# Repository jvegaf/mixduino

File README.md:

# Mixduino
An evolution of Open Source DJ MIDI Controllers
## Main Features
- 3 Complete Channels Mixer 
- 2 Decks  
- Library Browser with song preview function
- 16 Control Pads with RGB Leds (8/Deck)
- FX Controls
- 75 mm pitch/tempo controls
- Multitouch bars instead Jog Wheels
- Compact size enought to take in a backpack (360x260mm) 
## Note
This project actually are WIP.
## Previews

</br>

</br>

</br>

</br>

.
.
.

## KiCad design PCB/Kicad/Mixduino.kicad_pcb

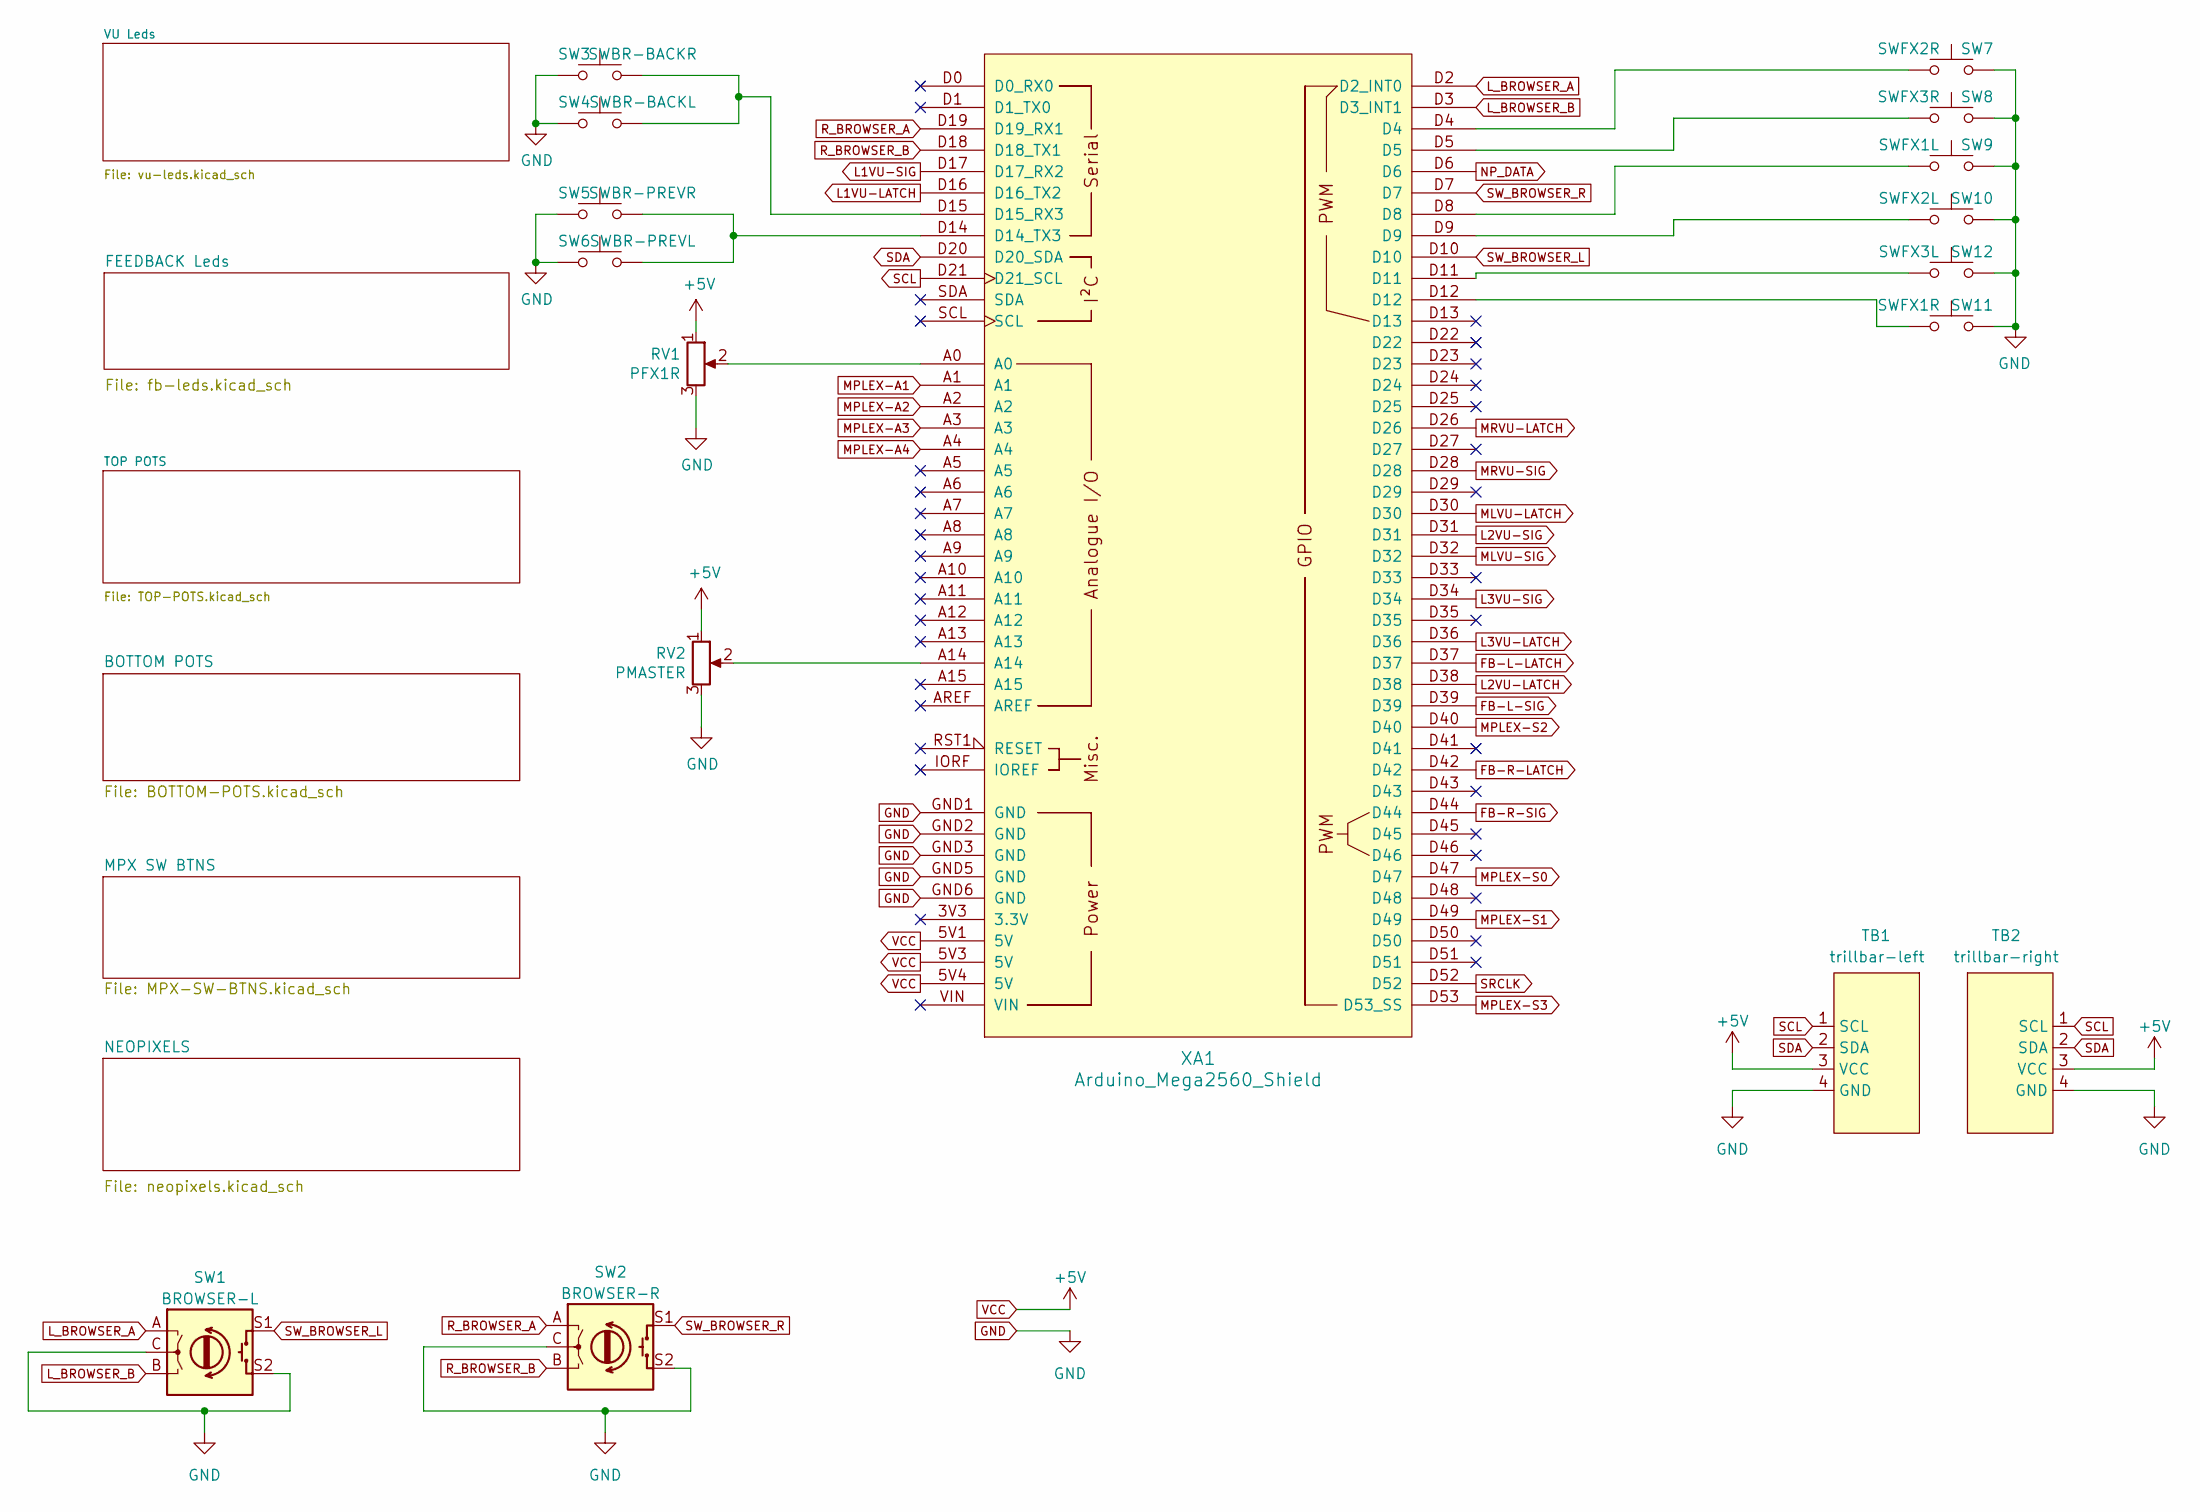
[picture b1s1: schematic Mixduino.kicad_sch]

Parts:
RV1: PFX1R; Potentiometer_Bourns_PTV09A-1_Single_Vertical
RV2: PMASTER; Potentiometer_Bourns_PTV09A-1_Single_Vertical
SW1: BROWSER-L; RotaryEncoder_Alps_EC11E-Switch_Vertical_H20mm_CircularMoun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
SW2: BROWSER-R; RotaryEncoder_Alps_EC11E-Switch_Vertical_H20mm_CircularMoun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
SW3: SWBR-BACKR; SW_Push_1P1T_NO_6x6mm_H8mm
SW4: SWBR-BACKL; SW_Push_1P1T_NO_6x6mm_H8mm
SW5: SWBR-PREVR; SW_Push_1P1T_NO_6x6mm_H8mm
SW6: SWBR-PREVL; SW_Push_1P1T_NO_6x6mm_H8mm
SW7: SWFX2R; SW_Push_1P1T_NO_6x6mm_H8mm
SW8: SWFX3R; SW_Push_1P1T_NO_6x6mm_H8mm
SW9: SWFX1L; SW_Push_1P1T_NO_6x6mm_H8mm
SW10: SWFX2L; SW_Push_1P1T_NO_6x6mm_H8mm
SW11: SWFX1R; SW_Push_1P1T_NO_6x6mm_H8mm
SW12: SWFX3L; SW_Push_1P1T_NO_6x6mm_H8mm
TB1: trillbar-left; JST_XHP_XH-A-1_1x04_P2.54mm_Horizontal
TB2: trillbar-right; JST_XHP_XH-A-1_1x04_P2.54mm_Horizontal
XA1: Arduino_Mega2560_Shield

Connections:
FB-L-LATCH: XA1.D37; also elsewhere on the board
FB-L-SIG: XA1.D39; also elsewhere on the board
FB-R-LATCH: XA1.D42; also elsewhere on the board
FB-R-SIG: XA1.D44; also elsewhere on the board
GND: RV1.3, RV2.3, SW1.C, SW1.S2, SW2.C, SW2.S2, SW3.1, SW4.1, SW5.1, SW6.1, SW7.1, SW8.1, SW9.1, SW10.1, SW11.1, SW12.1, TB1.4 (GND), TB2.4 (GND), XA1.GND1 (GND), XA1.GND2 (GND), XA1.GND3 (GND), XA1.GND5 (GND), XA1.GND6 (GND); also elsewhere on the board
L1VU-LATCH: XA1.D16 (D16_TX2); also elsewhere on the board
L1VU-SIG: XA1.D17 (D17_RX2); also elsewhere on the board
L2VU-LATCH: XA1.D38; also elsewhere on the board
L2VU-SIG: XA1.D31; also elsewhere on the board
L3VU-LATCH: XA1.D36; also elsewhere on the board
L3VU-SIG: XA1.D34; also elsewhere on the board
L_BROWSER_A: SW1.A, XA1.D2 (D2_INT0)
L_BROWSER_B: SW1.B, XA1.D3 (D3_INT1)
MLVU-LATCH: XA1.D30; also elsewhere on the board
MLVU-SIG: XA1.D32; also elsewhere on the board
MPLEX-A1: XA1.A1; also elsewhere on the board
MPLEX-A2: XA1.A2; also elsewhere on the board
MPLEX-A3: XA1.A3; also elsewhere on the board
MPLEX-A4: XA1.A4; also elsewhere on the board
MPLEX-S0: XA1.D47; also elsewhere on the board
MPLEX-S1: XA1.D49; also elsewhere on the board
MPLEX-S2: XA1.D40; also elsewhere on the board
MPLEX-S3: XA1.D53 (D53_SS); also elsewhere on the board
MRVU-LATCH: XA1.D26; also elsewhere on the board
MRVU-SIG: XA1.D28; also elsewhere on the board
NP_DATA: XA1.D6; also elsewhere on the board
unnamed: RV1.2, XA1.A0
unnamed: RV2.2, XA1.A14
unnamed: SW3.2, SW4.2, XA1.D15 (D15_RX3)
unnamed: SW5.2, SW6.2, XA1.D14 (D14_TX3)
unnamed: SW7.2, XA1.D4
unnamed: SW8.2, XA1.D5
unnamed: SW9.2, XA1.D8
unnamed: SW10.2, XA1.D9
unnamed: SW11.2, XA1.D12
unnamed: SW12.2, XA1.D11
R_BROWSER_A: SW2.A, XA1.D19 (D19_RX1)
R_BROWSER_B: SW2.B, XA1.D18 (D18_TX1)
SCL: TB1.1 (SCL), TB2.1 (SCL), XA1.D21 (D21_SCL)
SDA: TB1.2 (SDA), TB2.2 (SDA), XA1.D20 (D20_SDA)
SRCLK: XA1.D52; also elsewhere on the board
SW_BROWSER_L: SW1.S1, XA1.D10
SW_BROWSER_R: SW2.S1, XA1.D7
VCC: RV1.1, RV2.1, TB1.3 (VCC), TB2.3 (VCC), XA1.5V1 (5V), XA1.5V3 (5V), XA1.5V4 (5V); also elsewhere on the board

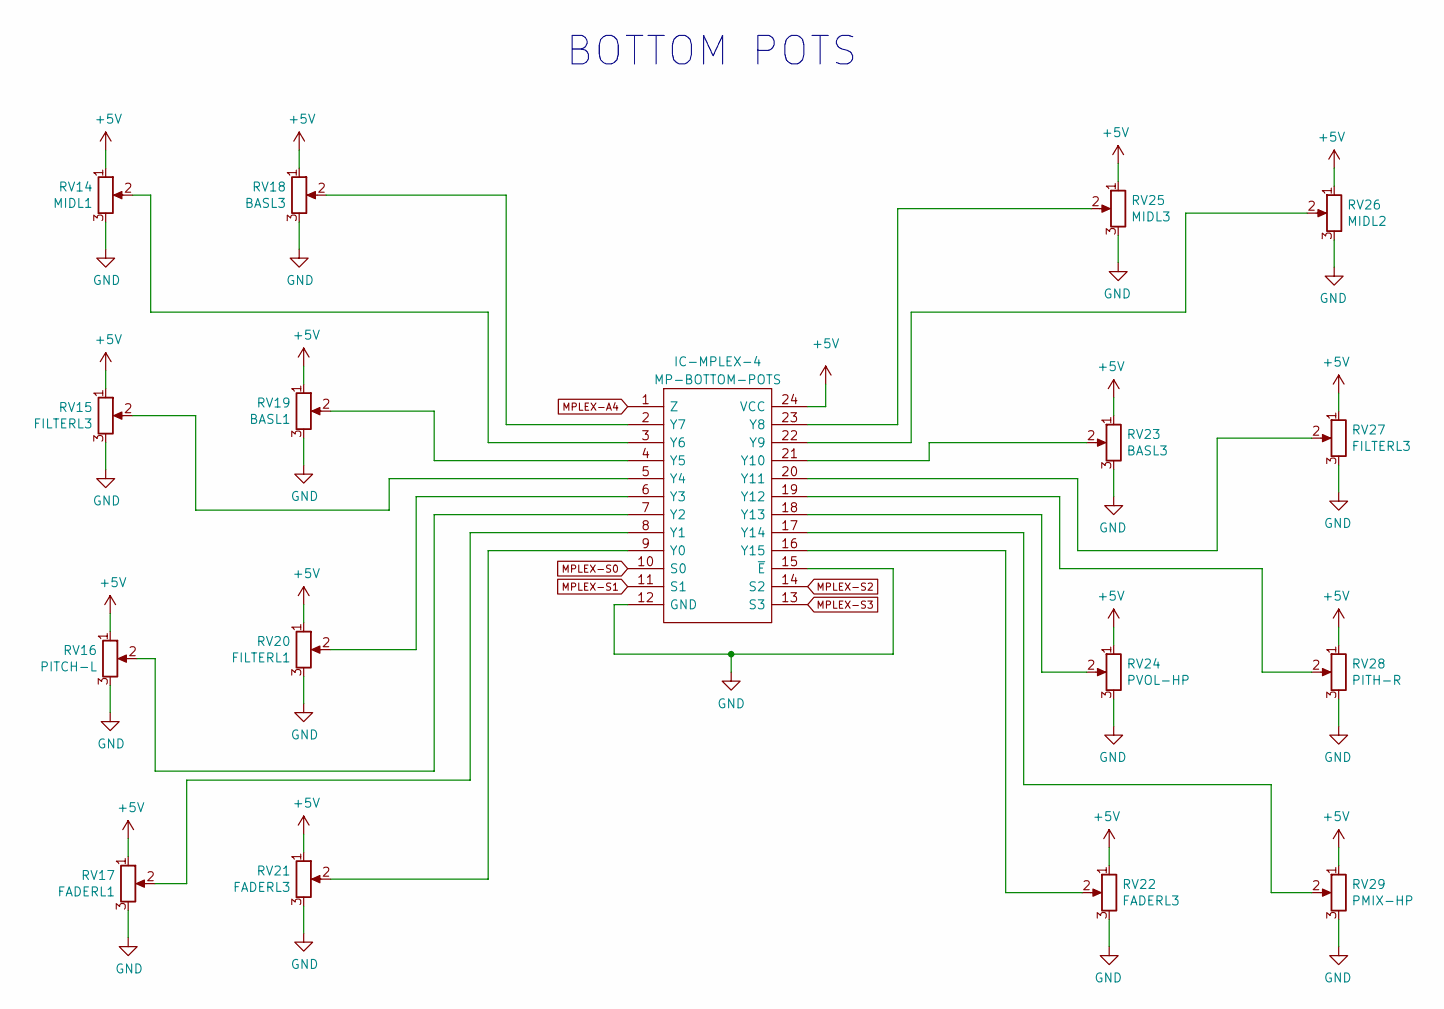
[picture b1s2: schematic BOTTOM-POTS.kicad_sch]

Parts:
IC-MPLEX-4: MP-BOTTOM-POTS; SOIC-24W_7.5x15.4mm_P1.27mm; Mouser Part Number 771-HC4067D653
RV14: MIDL1; Potentiometer_Bourns_PTV09A-1_Single_Vertical
RV15, RV27: FILTERL3; Potentiometer_Bourns_PTV09A-1_Single_Vertical
RV16: PITCH-L; fader-L75
RV17: FADERL1; fader-L60
RV18, RV23: BASL3; Potentiometer_Bourns_PTV09A-1_Single_Vertical
RV19: BASL1; Potentiometer_Bourns_PTV09A-1_Single_Vertical
RV20: FILTERL1; Potentiometer_Bourns_PTV09A-1_Single_Vertical
RV21, RV22: FADERL3; fader-L60
RV24: PVOL-HP; Potentiometer_Bourns_PTV09A-1_Single_Vertical
RV25: MIDL3; Potentiometer_Bourns_PTV09A-1_Single_Vertical
RV26: MIDL2; Potentiometer_Bourns_PTV09A-1_Single_Vertical
RV28: PITH-R; fader-L75
RV29: PMIX-HP; Potentiometer_Bourns_PTV09A-1_Single_Vertical

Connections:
GND: IC-MPLEX-4.12 (GND), IC-MPLEX-4.15 (~E), RV14.3, RV15.3, RV16.3, RV17.3, RV18.3, RV19.3, RV20.3, RV21.3, RV22.3, RV23.3, RV24.3, RV25.3, RV26.3, RV27.3, RV28.3, RV29.3; also elsewhere on the board
MPLEX-A4: IC-MPLEX-4.1 (Z); also elsewhere on the board
MPLEX-S0: IC-MPLEX-4.10 (S0); also elsewhere on the board
MPLEX-S1: IC-MPLEX-4.11 (S1); also elsewhere on the board
MPLEX-S2: IC-MPLEX-4.14 (S2); also elsewhere on the board
MPLEX-S3: IC-MPLEX-4.13 (S3); also elsewhere on the board
unnamed: IC-MPLEX-4.2 (Y7), RV18.2
unnamed: IC-MPLEX-4.3 (Y6), RV14.2
unnamed: IC-MPLEX-4.4 (Y5), RV19.2
unnamed: IC-MPLEX-4.5 (Y4), RV15.2
unnamed: IC-MPLEX-4.6 (Y3), RV20.2
unnamed: IC-MPLEX-4.7 (Y2), RV16.2
unnamed: IC-MPLEX-4.8 (Y1), RV17.2
unnamed: IC-MPLEX-4.9 (Y0), RV21.2
unnamed: IC-MPLEX-4.16 (Y15), RV22.2
unnamed: IC-MPLEX-4.17 (Y14), RV29.2
unnamed: IC-MPLEX-4.18 (Y13), RV24.2
unnamed: IC-MPLEX-4.19 (Y12), RV28.2
unnamed: IC-MPLEX-4.20 (Y11), RV27.2
unnamed: IC-MPLEX-4.21 (Y10), RV23.2
unnamed: IC-MPLEX-4.22 (Y9), RV26.2
unnamed: IC-MPLEX-4.23 (Y8), RV25.2
VCC: IC-MPLEX-4.24 (VCC), RV14.1, RV15.1, RV16.1, RV17.1, RV18.1, RV19.1, RV20.1, RV21.1, RV22.1, RV23.1, RV24.1, RV25.1, RV26.1, RV27.1, RV28.1, RV29.1; also elsewhere on the board

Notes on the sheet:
BOTTOM POTS

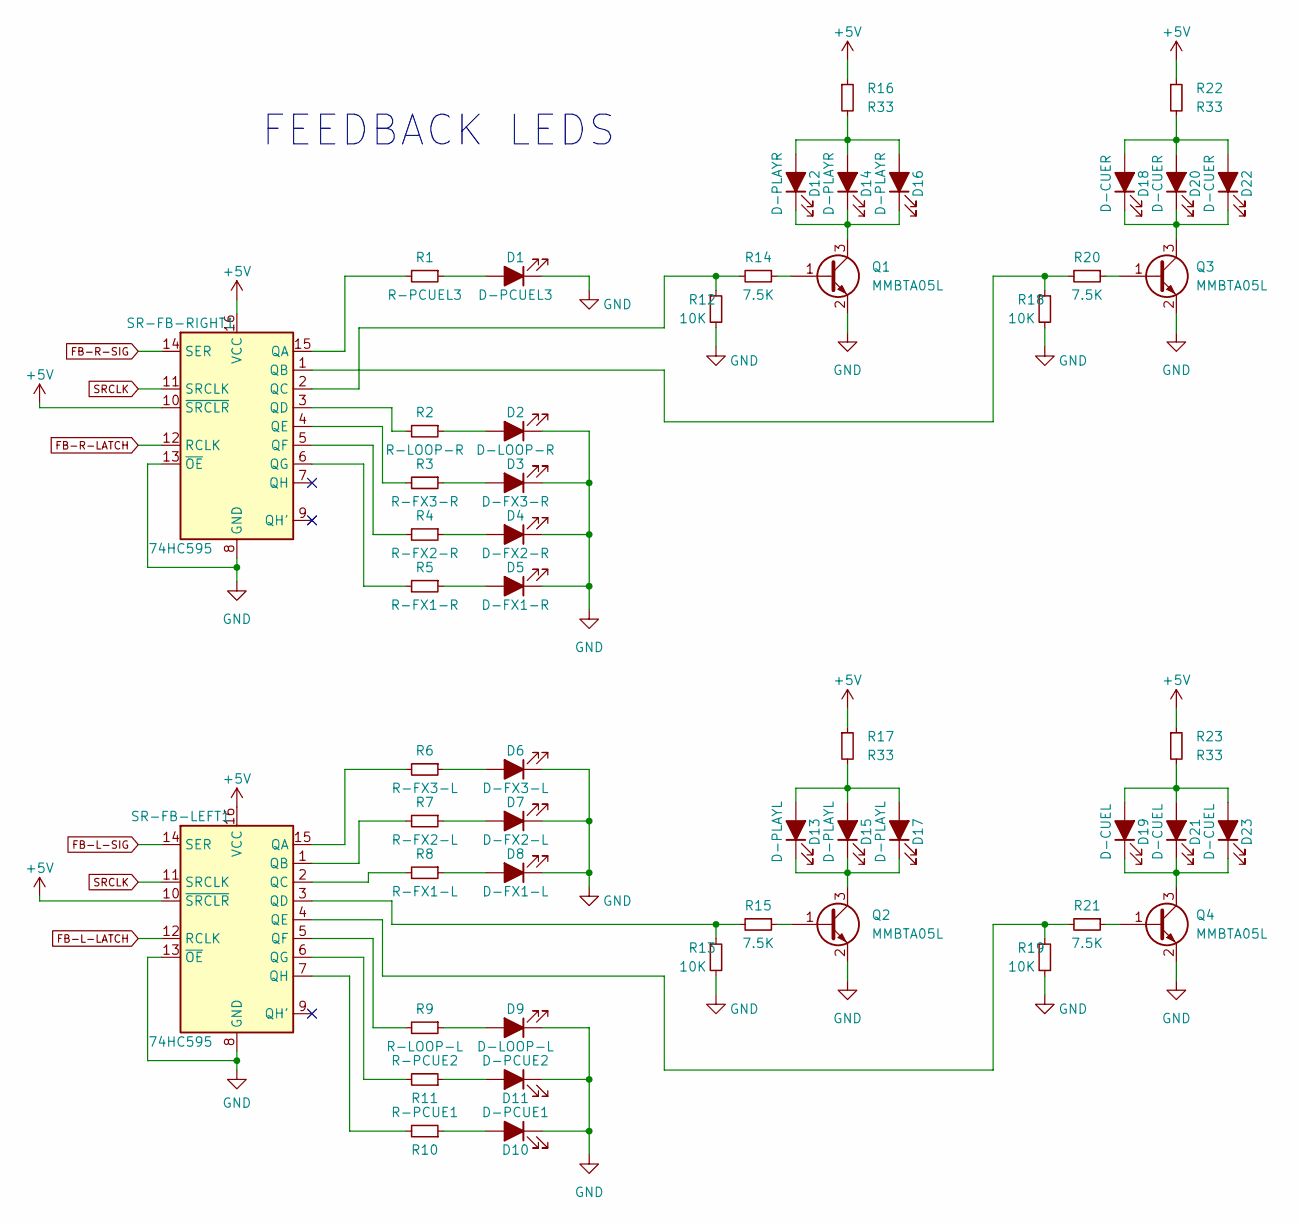
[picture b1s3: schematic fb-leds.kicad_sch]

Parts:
D1: D-PCUEL3; LED_1206_3216Metric_Pad1.42x1.75mm_HandSolder
D2: D-LOOP-R; LED_1206_3216Metric_Pad1.42x1.75mm_HandSolder
D3: D-FX3-R; LED_1206_3216Metric_Pad1.42x1.75mm_HandSolder
D4: D-FX2-R; LED_1206_3216Metric_Pad1.42x1.75mm_HandSolder
D5: D-FX1-R; LED_1206_3216Metric_Pad1.42x1.75mm_HandSolder
D6: D-FX3-L; LED_1206_3216Metric_Pad1.42x1.75mm_HandSolder
D7: D-FX2-L; LED_1206_3216Metric_Pad1.42x1.75mm_HandSolder
D8: D-FX1-L; LED_1206_3216Metric_Pad1.42x1.75mm_HandSolder
D9: D-LOOP-L; LED_1206_3216Metric_Pad1.42x1.75mm_HandSolder
D10: D-PCUE1; LED_1206_3216Metric_Pad1.42x1.75mm_HandSolder
D11: D-PCUE2; LED_1206_3216Metric_Pad1.42x1.75mm_HandSolder
D12, D14, D16: D-PLAYR; LED_1206_3216Metric_Pad1.42x1.75mm_HandSolder
D13, D15, D17: D-PLAYL; LED_1206_3216Metric_Pad1.42x1.75mm_HandSolder
D18, D20, D22: D-CUER; LED_1206_3216Metric_Pad1.42x1.75mm_HandSolder
D19, D21, D23: D-CUEL; LED_1206_3216Metric_Pad1.42x1.75mm_HandSolder
Q1, Q2, Q3, Q4: MMBTA05L; SOT-23_Handsoldering
R1: R-PCUEL3; R_1206_3216Metric_Pad1.30x1.75mm_HandSolder
R2: R-LOOP-R; R_1206_3216Metric_Pad1.30x1.75mm_HandSolder
R3: R-FX3-R; R_1206_3216Metric_Pad1.30x1.75mm_HandSolder
R4: R-FX2-R; R_1206_3216Metric_Pad1.30x1.75mm_HandSolder
R5: R-FX1-R; R_1206_3216Metric_Pad1.30x1.75mm_HandSolder
R6: R-FX3-L; R_1206_3216Metric_Pad1.30x1.75mm_HandSolder
R7: R-FX2-L; R_1206_3216Metric_Pad1.30x1.75mm_HandSolder
R8: R-FX1-L; R_1206_3216Metric_Pad1.30x1.75mm_HandSolder
R9: R-LOOP-L; R_1206_3216Metric_Pad1.30x1.75mm_HandSolder
R10: R-PCUE1; R_1206_3216Metric_Pad1.30x1.75mm_HandSolder
R11: R-PCUE2; R_1206_3216Metric_Pad1.30x1.75mm_HandSolder
R12, R13, R18, R19: 10K; R_1206_3216Metric_Pad1.30x1.75mm_HandSolder
R14, R15, R20, R21: 7.5K; R_1206_3216Metric_Pad1.30x1.75mm_HandSolder
R16, R17, R22, R23: R33; R_1206_3216Metric_Pad1.30x1.75mm_HandSolder
SR-FB-LEFT1: 74HC595; SO-16_3.9x9.9mm_P1.27mm
SR-FB-RIGHT1: 74HC595; SO-16_3.9x9.9mm_P1.27mm

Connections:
FB-L-LATCH: SR-FB-LEFT1.12 (RCLK); also elsewhere on the board
FB-L-SIG: SR-FB-LEFT1.14 (SER); also elsewhere on the board
FB-R-LATCH: SR-FB-RIGHT1.12 (RCLK); also elsewhere on the board
FB-R-SIG: SR-FB-RIGHT1.14 (SER); also elsewhere on the board
GND: D1.1 (K), D2.1 (K), D3.1 (K), D4.1 (K), D5.1 (K), D6.1 (K), D7.1 (K), D8.1 (K), D9.1 (K), D10.1 (K), D11.1 (K), Q1.2 (E), Q2.2 (E), Q3.2 (E), Q4.2 (E), R12.2, R13.2, R18.2, R19.2, SR-FB-LEFT1.8 (GND), SR-FB-LEFT1.13 (~OE), SR-FB-RIGHT1.8 (GND), SR-FB-RIGHT1.13 (~OE); also elsewhere on the board
unnamed: D1.2 (A), R1.1
unnamed: D2.2 (A), R2.1
unnamed: D3.2 (A), R3.1
unnamed: D4.2 (A), R4.1
unnamed: D5.2 (A), R5.1
unnamed: D6.2 (A), R6.1
unnamed: D7.2 (A), R7.1
unnamed: D8.2 (A), R8.1
unnamed: D9.2 (A), R9.1
unnamed: D10.2 (A), R10.1
unnamed: D11.2 (A), R11.1
unnamed: D12.1 (K), D14.1 (K), D16.1 (K), Q1.3 (C)
unnamed: D12.2 (A), D14.2 (A), D16.2 (A), R16.2
unnamed: D13.1 (K), D15.1 (K), D17.1 (K), Q2.3 (C)
unnamed: D13.2 (A), D15.2 (A), D17.2 (A), R17.2
unnamed: D18.1 (K), D20.1 (K), D22.1 (K), Q3.3 (C)
unnamed: D18.2 (A), D20.2 (A), D22.2 (A), R22.2
unnamed: D19.1 (K), D21.1 (K), D23.1 (K), Q4.3 (C)
unnamed: D19.2 (A), D21.2 (A), D23.2 (A), R23.2
unnamed: Q1.1 (B), R14.1
unnamed: Q2.1 (B), R15.1
unnamed: Q3.1 (B), R20.1
unnamed: Q4.1 (B), R21.1
unnamed: R1.2, SR-FB-RIGHT1.15 (QA)
unnamed: R2.2, SR-FB-RIGHT1.3 (QD)
unnamed: R3.2, SR-FB-RIGHT1.4 (QE)
unnamed: R4.2, SR-FB-RIGHT1.5 (QF)
unnamed: R5.2, SR-FB-RIGHT1.6 (QG)
unnamed: R6.2, SR-FB-LEFT1.15 (QA)
unnamed: R7.2, SR-FB-LEFT1.1 (QB)
unnamed: R8.2, SR-FB-LEFT1.2 (QC)
unnamed: R9.2, SR-FB-LEFT1.5 (QF)
unnamed: R10.2, SR-FB-LEFT1.7 (QH)
unnamed: R11.2, SR-FB-LEFT1.6 (QG)
unnamed: R12.1, R14.2, SR-FB-RIGHT1.2 (QC)
unnamed: R13.1, R15.2, SR-FB-LEFT1.3 (QD)
unnamed: R18.1, R20.2, SR-FB-RIGHT1.1 (QB)
unnamed: R19.1, R21.2, SR-FB-LEFT1.4 (QE)
SRCLK: SR-FB-LEFT1.11 (SRCLK), SR-FB-RIGHT1.11 (SRCLK); also elsewhere on the board
VCC: R16.1, R17.1, R22.1, R23.1, SR-FB-LEFT1.10 (~SRCLR), SR-FB-LEFT1.16 (VCC), SR-FB-RIGHT1.10 (~SRCLR), SR-FB-RIGHT1.16 (VCC); also elsewhere on the board

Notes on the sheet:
FEEDBACK LEDS

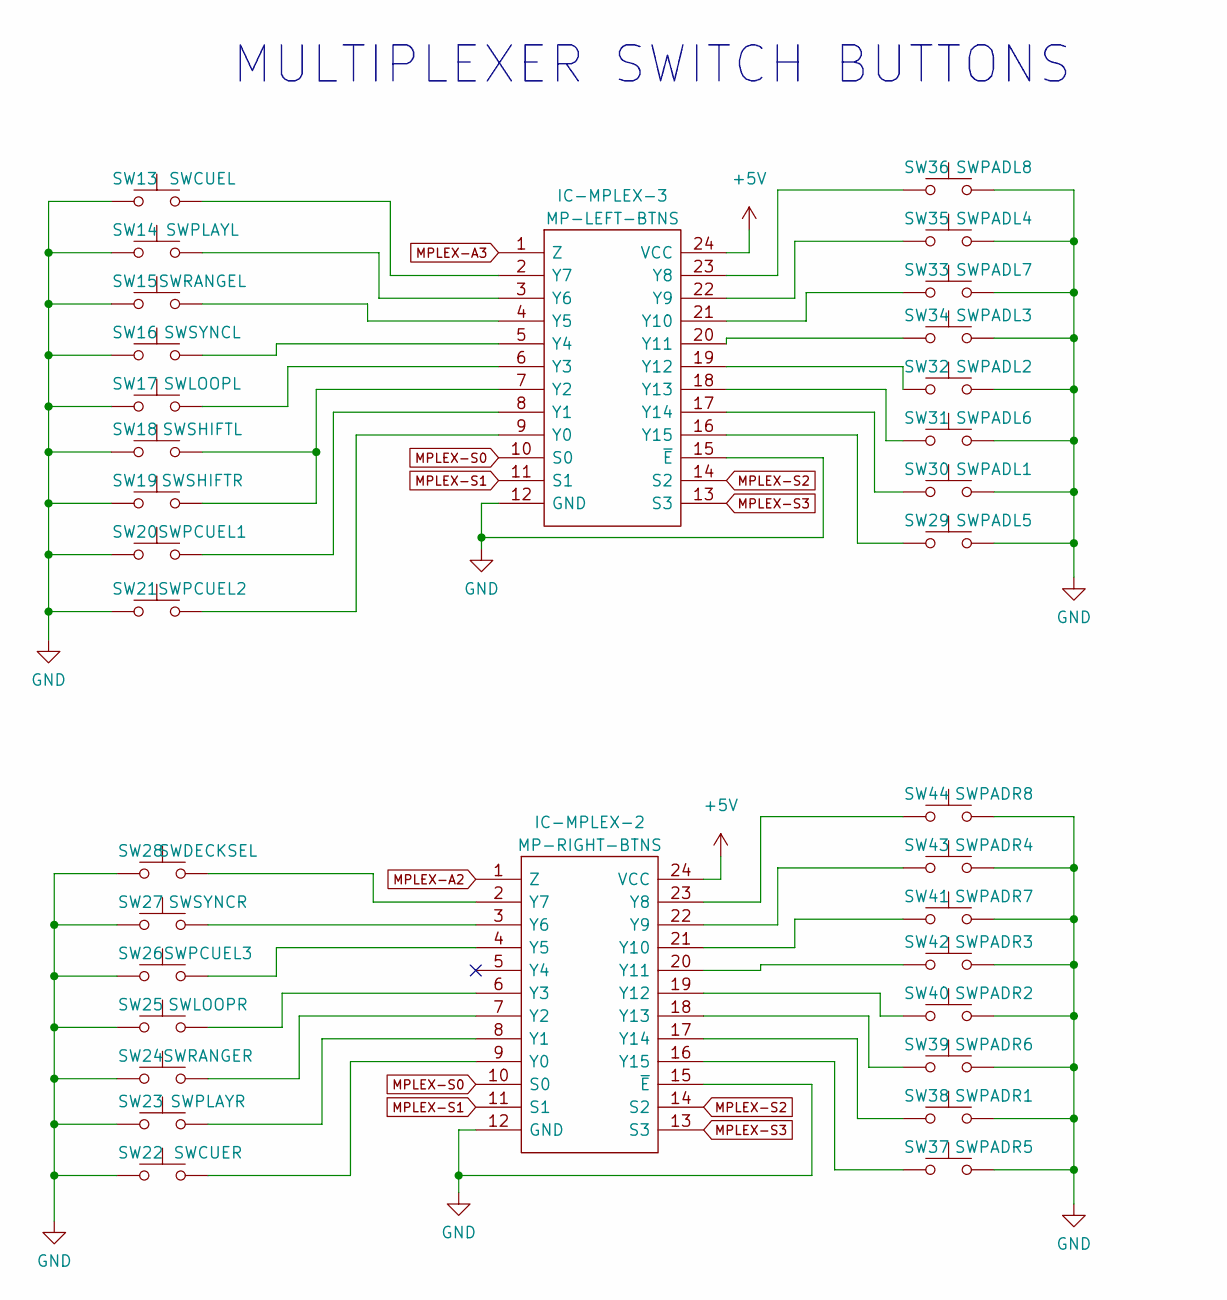
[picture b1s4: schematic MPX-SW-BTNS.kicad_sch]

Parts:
IC-MPLEX-2: MP-RIGHT-BTNS; SOIC-24W_7.5x15.4mm_P1.27mm; Mouser Part Number 771-HC4067D653
IC-MPLEX-3: MP-LEFT-BTNS; SOIC-24W_7.5x15.4mm_P1.27mm; Mouser Part Number 771-HC4067D653
SW13: SWCUEL; SW_Push_1P1T_NO_6x6mm_H8mm
SW14: SWPLAYL; SW_Push_1P1T_NO_6x6mm_H8mm
SW15: SWRANGEL; SW_Push_1P1T_NO_6x6mm_H8mm
SW16: SWSYNCL; SW_Push_1P1T_NO_6x6mm_H8mm
SW17: SWLOOPL; SW_Push_1P1T_NO_6x6mm_H8mm
SW18: SWSHIFTL; SW_Push_1P1T_NO_6x6mm_H8mm
SW19: SWSHIFTR; SW_Push_1P1T_NO_6x6mm_H8mm
SW20: SWPCUEL1; SW_Push_1P1T_NO_6x6mm_H8mm
SW21: SWPCUEL2; SW_Push_1P1T_NO_6x6mm_H8mm
SW22: SWCUER; SW_Push_1P1T_NO_6x6mm_H8mm
SW23: SWPLAYR; SW_Push_1P1T_NO_6x6mm_H8mm
SW24: SWRANGER; SW_Push_1P1T_NO_6x6mm_H8mm
SW25: SWLOOPR; SW_Push_1P1T_NO_6x6mm_H8mm
SW26: SWPCUEL3; SW_Push_1P1T_NO_6x6mm_H8mm
SW27: SWSYNCR; SW_Push_1P1T_NO_6x6mm_H8mm
SW28: SWDECKSEL; SW_Push_1P1T_NO_6x6mm_H8mm
SW29: SWPADL5; sw-pad
SW30: SWPADL1; sw-pad
SW31: SWPADL6; sw-pad
SW32: SWPADL2; sw-pad
SW33: SWPADL7; sw-pad
SW34: SWPADL3; sw-pad
SW35: SWPADL4; sw-pad
SW36: SWPADL8; sw-pad
SW37: SWPADR5; sw-pad
SW38: SWPADR1; sw-pad
SW39: SWPADR6; sw-pad
SW40: SWPADR2; sw-pad
SW41: SWPADR7; sw-pad
SW42: SWPADR3; sw-pad
SW43: SWPADR4; sw-pad
SW44: SWPADR8; sw-pad

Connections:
GND: IC-MPLEX-2.12 (GND), IC-MPLEX-2.15 (~E), IC-MPLEX-3.12 (GND), IC-MPLEX-3.15 (~E), SW13.1, SW14.1, SW15.1, SW16.1, SW17.1, SW18.1, SW19.1, SW20.1, SW21.1, SW22.1, SW23.1, SW24.1, SW25.1, SW26.1, SW27.1, SW28.1, SW29.2, SW30.2, SW31.2, SW32.2, SW33.2, SW34.2, SW35.2, SW36.2, SW37.2, SW38.2, SW39.2, SW40.2, SW41.2, SW42.2, SW43.2, SW44.2; also elsewhere on the board
MPLEX-A2: IC-MPLEX-2.1 (Z); also elsewhere on the board
MPLEX-A3: IC-MPLEX-3.1 (Z); also elsewhere on the board
MPLEX-S0: IC-MPLEX-2.10 (S0), IC-MPLEX-3.10 (S0); also elsewhere on the board
MPLEX-S1: IC-MPLEX-2.11 (S1), IC-MPLEX-3.11 (S1); also elsewhere on the board
MPLEX-S2: IC-MPLEX-2.14 (S2), IC-MPLEX-3.14 (S2); also elsewhere on the board
MPLEX-S3: IC-MPLEX-2.13 (S3), IC-MPLEX-3.13 (S3); also elsewhere on the board
unnamed: IC-MPLEX-2.2 (Y7), SW28.2
unnamed: IC-MPLEX-2.3 (Y6), SW27.2
unnamed: IC-MPLEX-2.4 (Y5), SW26.2
unnamed: IC-MPLEX-2.6 (Y3), SW25.2
unnamed: IC-MPLEX-2.7 (Y2), SW24.2
unnamed: IC-MPLEX-2.8 (Y1), SW23.2
unnamed: IC-MPLEX-2.9 (Y0), SW22.2
unnamed: IC-MPLEX-2.16 (Y15), SW37.1
unnamed: IC-MPLEX-2.17 (Y14), SW38.1
unnamed: IC-MPLEX-2.18 (Y13), SW39.1
unnamed: IC-MPLEX-2.19 (Y12), SW40.1
unnamed: IC-MPLEX-2.20 (Y11), SW42.1
unnamed: IC-MPLEX-2.21 (Y10), SW41.1
unnamed: IC-MPLEX-2.22 (Y9), SW43.1
unnamed: IC-MPLEX-2.23 (Y8), SW44.1
unnamed: IC-MPLEX-3.2 (Y7), SW13.2
unnamed: IC-MPLEX-3.3 (Y6), SW14.2
unnamed: IC-MPLEX-3.4 (Y5), SW15.2
unnamed: IC-MPLEX-3.5 (Y4), SW16.2
unnamed: IC-MPLEX-3.6 (Y3), SW17.2
unnamed: IC-MPLEX-3.7 (Y2), SW18.2, SW19.2
unnamed: IC-MPLEX-3.8 (Y1), SW20.2
unnamed: IC-MPLEX-3.9 (Y0), SW21.2
unnamed: IC-MPLEX-3.16 (Y15), SW29.1
unnamed: IC-MPLEX-3.17 (Y14), SW30.1
unnamed: IC-MPLEX-3.18 (Y13), SW31.1
unnamed: IC-MPLEX-3.19 (Y12), SW32.1
unnamed: IC-MPLEX-3.20 (Y11), SW34.1
unnamed: IC-MPLEX-3.21 (Y10), SW33.1
unnamed: IC-MPLEX-3.22 (Y9), SW35.1
unnamed: IC-MPLEX-3.23 (Y8), SW36.1
VCC: IC-MPLEX-2.24 (VCC), IC-MPLEX-3.24 (VCC); also elsewhere on the board

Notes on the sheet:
MULTIPLEXER SWITCH BUTTONS

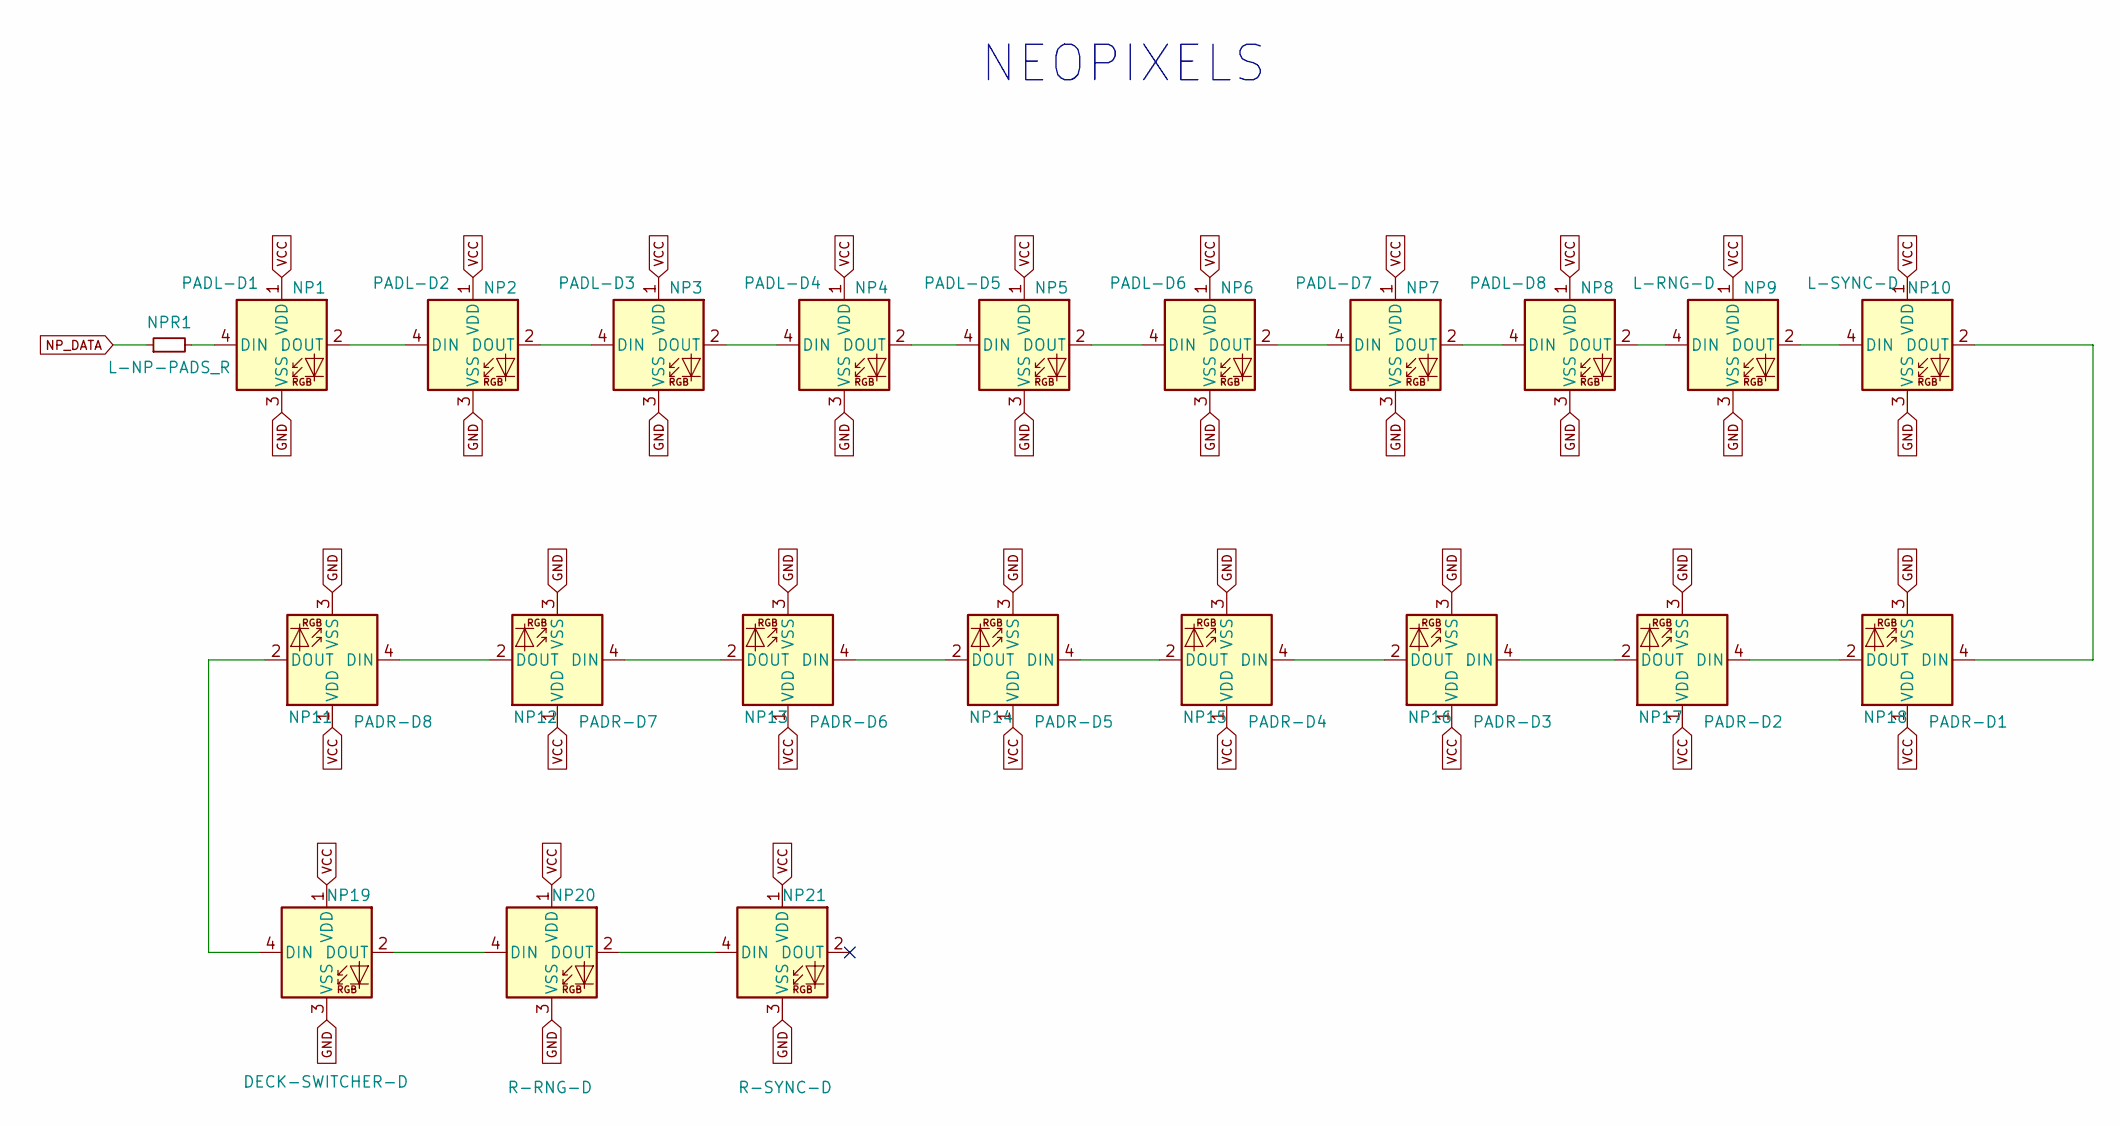
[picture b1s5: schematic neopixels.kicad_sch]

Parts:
NP1: PADL-D1; LED_WS2812B_PLCC4_5.0x5.0mm_P3.2mm
NP2: PADL-D2; LED_WS2812B_PLCC4_5.0x5.0mm_P3.2mm
NP3: PADL-D3; LED_WS2812B_PLCC4_5.0x5.0mm_P3.2mm
NP4: PADL-D4; LED_WS2812B_PLCC4_5.0x5.0mm_P3.2mm
NP5: PADL-D5; LED_WS2812B_PLCC4_5.0x5.0mm_P3.2mm
NP6: PADL-D6; LED_WS2812B_PLCC4_5.0x5.0mm_P3.2mm
NP7: PADL-D7; LED_WS2812B_PLCC4_5.0x5.0mm_P3.2mm
NP8: PADL-D8; LED_WS2812B_PLCC4_5.0x5.0mm_P3.2mm
NP9: L-RNG-D; LED_WS2812B_PLCC4_5.0x5.0mm_P3.2mm
NP10: L-SYNC-D; LED_WS2812B_PLCC4_5.0x5.0mm_P3.2mm
NP11: PADR-D8; LED_WS2812B_PLCC4_5.0x5.0mm_P3.2mm
NP12: PADR-D7; LED_WS2812B_PLCC4_5.0x5.0mm_P3.2mm
NP13: PADR-D6; LED_WS2812B_PLCC4_5.0x5.0mm_P3.2mm
NP14: PADR-D5; LED_WS2812B_PLCC4_5.0x5.0mm_P3.2mm
NP15: PADR-D4; LED_WS2812B_PLCC4_5.0x5.0mm_P3.2mm
NP16: PADR-D3; LED_WS2812B_PLCC4_5.0x5.0mm_P3.2mm
NP17: PADR-D2; LED_WS2812B_PLCC4_5.0x5.0mm_P3.2mm
NP18: PADR-D1; LED_WS2812B_PLCC4_5.0x5.0mm_P3.2mm
NP19: DECK-SWITCHER-D; LED_WS2812B_PLCC4_5.0x5.0mm_P3.2mm
NP20: R-RNG-D; LED_WS2812B_PLCC4_5.0x5.0mm_P3.2mm
NP21: R-SYNC-D; LED_WS2812B_PLCC4_5.0x5.0mm_P3.2mm
NPR1: L-NP-PADS_R; R_1206_3216Metric_Pad1.30x1.75mm_HandSolder

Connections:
GND: NP1.3 (VSS), NP2.3 (VSS), NP3.3 (VSS), NP4.3 (VSS), NP5.3 (VSS), NP6.3 (VSS), NP7.3 (VSS), NP8.3 (VSS), NP9.3 (VSS), NP10.3 (VSS), NP11.3 (VSS), NP12.3 (VSS), NP13.3 (VSS), NP14.3 (VSS), NP15.3 (VSS), NP16.3 (VSS), NP17.3 (VSS), NP18.3 (VSS), NP19.3 (VSS), NP20.3 (VSS), NP21.3 (VSS); also elsewhere on the board
NP_DATA: NPR1.1; also elsewhere on the board
unnamed: NP1.2 (DOUT), NP2.4 (DIN)
unnamed: NP1.4 (DIN), NPR1.2
unnamed: NP2.2 (DOUT), NP3.4 (DIN)
unnamed: NP3.2 (DOUT), NP4.4 (DIN)
unnamed: NP4.2 (DOUT), NP5.4 (DIN)
unnamed: NP5.2 (DOUT), NP6.4 (DIN)
unnamed: NP6.2 (DOUT), NP7.4 (DIN)
unnamed: NP7.2 (DOUT), NP8.4 (DIN)
unnamed: NP8.2 (DOUT), NP9.4 (DIN)
unnamed: NP10.2 (DOUT), NP18.4 (DIN)
unnamed: NP9.2 (DOUT), NP10.4 (DIN)
unnamed: NP11.2 (DOUT), NP19.4 (DIN)
unnamed: NP11.4 (DIN), NP12.2 (DOUT)
unnamed: NP12.4 (DIN), NP13.2 (DOUT)
unnamed: NP13.4 (DIN), NP14.2 (DOUT)
unnamed: NP14.4 (DIN), NP15.2 (DOUT)
unnamed: NP15.4 (DIN), NP16.2 (DOUT)
unnamed: NP16.4 (DIN), NP17.2 (DOUT)
unnamed: NP17.4 (DIN), NP18.2 (DOUT)
unnamed: NP19.2 (DOUT), NP20.4 (DIN)
unnamed: NP20.2 (DOUT), NP21.4 (DIN)
VCC: NP1.1 (VDD), NP2.1 (VDD), NP3.1 (VDD), NP4.1 (VDD), NP5.1 (VDD), NP6.1 (VDD), NP7.1 (VDD), NP8.1 (VDD), NP9.1 (VDD), NP10.1 (VDD), NP11.1 (VDD), NP12.1 (VDD), NP13.1 (VDD), NP14.1 (VDD), NP15.1 (VDD), NP16.1 (VDD), NP17.1 (VDD), NP18.1 (VDD), NP19.1 (VDD), NP20.1 (VDD), NP21.1 (VDD); also elsewhere on the board

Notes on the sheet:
NEOPIXELS

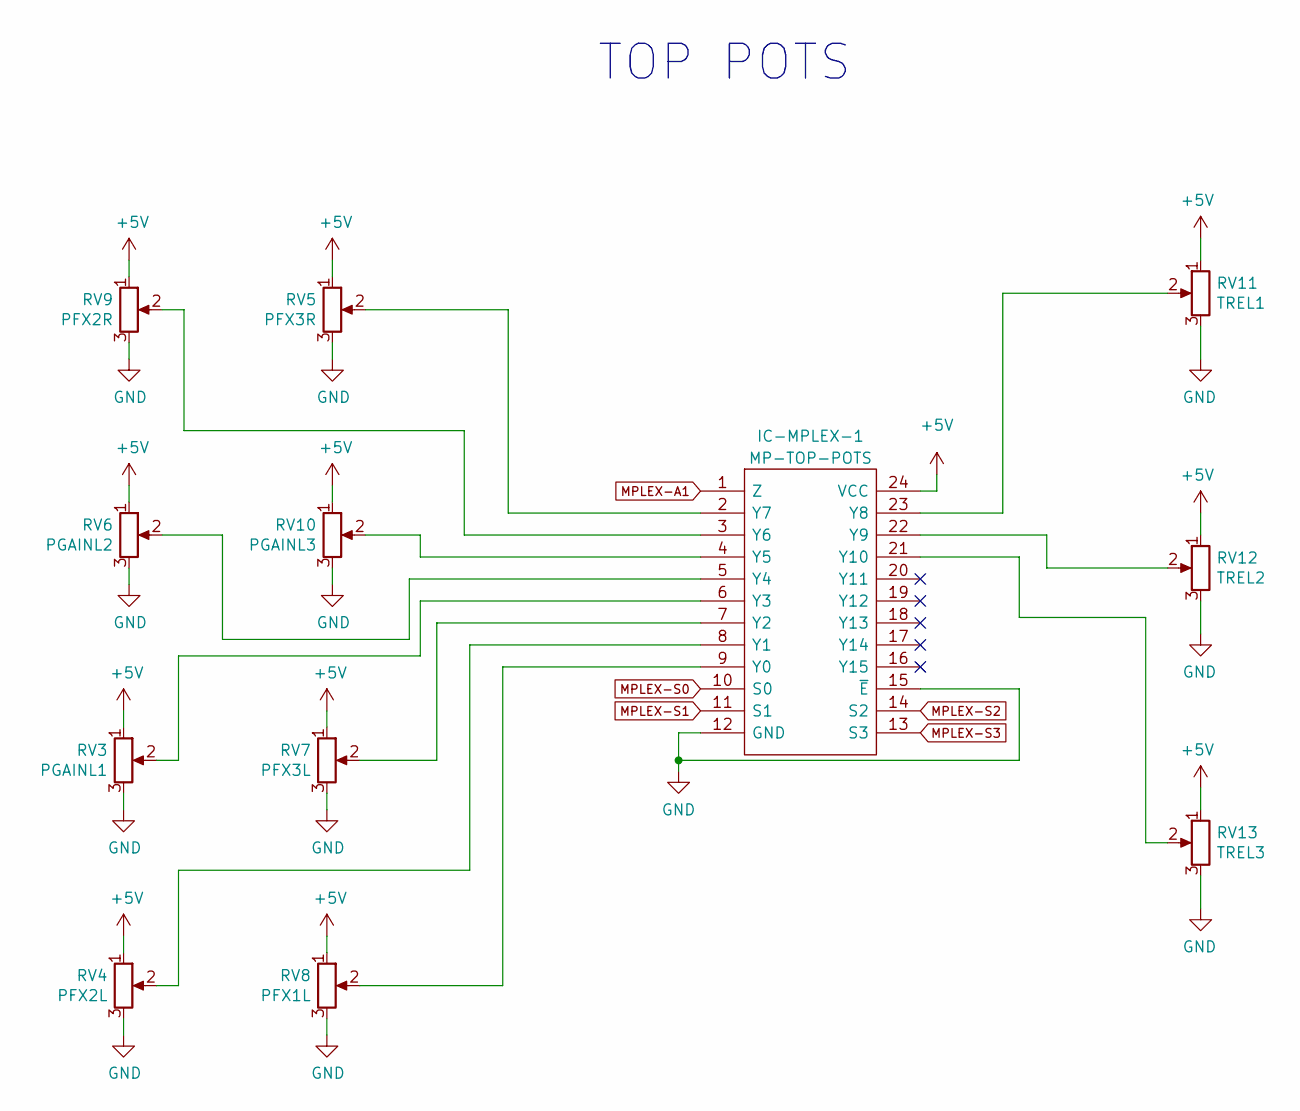
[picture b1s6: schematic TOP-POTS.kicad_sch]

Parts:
IC-MPLEX-1: MP-TOP-POTS; SOIC-24W_7.5x15.4mm_P1.27mm; Mouser Part Number 771-HC4067D653
RV3: PGAINL1; Potentiometer_Bourns_PTV09A-1_Single_Vertical
RV4: PFX2L; Potentiometer_Bourns_PTV09A-1_Single_Vertical
RV5: PFX3R; Potentiometer_Bourns_PTV09A-1_Single_Vertical
RV6: PGAINL2; Potentiometer_Bourns_PTV09A-1_Single_Vertical
RV7: PFX3L; Potentiometer_Bourns_PTV09A-1_Single_Vertical
RV8: PFX1L; Potentiometer_Bourns_PTV09A-1_Single_Vertical
RV9: PFX2R; Potentiometer_Bourns_PTV09A-1_Single_Vertical
RV10: PGAINL3; Potentiometer_Bourns_PTV09A-1_Single_Vertical
RV11: TREL1; Potentiometer_Bourns_PTV09A-1_Single_Vertical
RV12: TREL2; Potentiometer_Bourns_PTV09A-1_Single_Vertical
RV13: TREL3; Potentiometer_Bourns_PTV09A-1_Single_Vertical

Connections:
GND: IC-MPLEX-1.12 (GND), IC-MPLEX-1.15 (~E), RV3.3, RV4.3, RV5.3, RV6.3, RV7.3, RV8.3, RV9.3, RV10.3, RV11.3, RV12.3, RV13.3; also elsewhere on the board
MPLEX-A1: IC-MPLEX-1.1 (Z); also elsewhere on the board
MPLEX-S0: IC-MPLEX-1.10 (S0); also elsewhere on the board
MPLEX-S1: IC-MPLEX-1.11 (S1); also elsewhere on the board
MPLEX-S2: IC-MPLEX-1.14 (S2); also elsewhere on the board
MPLEX-S3: IC-MPLEX-1.13 (S3); also elsewhere on the board
unnamed: IC-MPLEX-1.2 (Y7), RV5.2
unnamed: IC-MPLEX-1.3 (Y6), RV9.2
unnamed: IC-MPLEX-1.4 (Y5), RV10.2
unnamed: IC-MPLEX-1.5 (Y4), RV6.2
unnamed: IC-MPLEX-1.6 (Y3), RV3.2
unnamed: IC-MPLEX-1.7 (Y2), RV7.2
unnamed: IC-MPLEX-1.8 (Y1), RV4.2
unnamed: IC-MPLEX-1.9 (Y0), RV8.2
unnamed: IC-MPLEX-1.21 (Y10), RV13.2
unnamed: IC-MPLEX-1.22 (Y9), RV12.2
unnamed: IC-MPLEX-1.23 (Y8), RV11.2
VCC: IC-MPLEX-1.24 (VCC), RV3.1, RV4.1, RV5.1, RV6.1, RV7.1, RV8.1, RV9.1, RV10.1, RV11.1, RV12.1, RV13.1; also elsewhere on the board

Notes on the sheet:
TOP POTS
